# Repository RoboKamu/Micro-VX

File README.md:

<h1 align="center"> Micro-VX: Mini Audio Visualizer </h1>

<div align="center">
<i> Small portable STM32L4 based audio wave and FFT visualizer from electret microphone. This project started as an experiment to design my first PCB and explore the STM32L4 low-power MCU family. </i>
</div>

---

> This repository includes an extra project on the same board. The accelerometer visualization. That project was for expirementing with the module for future use. The main purpose for the board is for it to be used with the microphone, however a PCB error ment it had to be modified after assembly.
>

> Demo for expirimental Accelerometer Visualization:  
>
> Demo for FFT and Auido Wave Visualization: [Youtube Video Link](https://www.youtube.com/watch?v=JHZs5dUxs48)

---

### 1. Project structure

#### 1.1 Hardware

All Kicad source files for Schematic and PCB files are in the hardware folder. Also including Gerber files and footprint placement (assembly) for direct manufacturing, in this case JLCPCB. 

There are 2 versions of the PCB, with one being modified after assembly.

* **Accelerometer visualization:** 
Original PCB according to the schematic. Utilizing the Accelerometer (3-axis LIS2DW12) and I2C pin headers for OLED display (SSD1306).

* **Audio analyzer:**
Modified after assembly (refer to hardware folder). The PCB used for the audio analysis with electret microphone (B4013AM423-093). Also utilizes the I2C pin headers for OLED display (SSD1306) and a mechanical switch to change program state. 

#### 1.2 Firmware

In the firmware folder you will see 2 projects: 

* **The STM32L4-LIS2DW12-Visual project in the STM32L4-Accelerometer-Visual folder:**
Visualizer for the cheap accelerometer I added to the PCB. The program just shows the X, Y and Z axis as well as temperature. Another detail is to measure VDDA, this is very useful for sampling with ADC on battery powered devices. Ensuring accurate scaling. 

* **STM32L4-FW :**
The main project is this audio wave and FFT visualizer. Depending on the mechanical switch state (read from EXTI callback) it can either be showing continous audio wave or the FFT representation of it. Includes TIMER2 peripheral for triggering ADC to sample microphone, DMA double buffering, and I2C protocol for OLED display. The MCU was programmed with a ST-LINK V2, developed in STM32cubeIDE with HAL, and used the ARM cmsis library for DSP applications. 

### 2. Hardware Architecture
The PCB includes ESD protection and reverse polarity protection. Safe to use even if both battery and USB is connected because of the schottcky diode "OR", and the onboard LDO ensures a stable voltage for the STM32.  

Refer to the hardware folder for more specific information about the post assembly modification. 

The STM32L4 was chosen because it is from the low power series and also includes FPU and DSP. Not much flash memory is needed here so the 32 KB flash size was chosen. 

### 3. Firmware Architecture

#### 3.1 STM32L4-FW 

The firmware is rather simple. Timer2 TRGO initiate a conversion with a sample rate of 50 kHz. The ADC uses 8x oversampling with 1 bit shift to compensate low gain on hardware. DMA double buffer is used so wave visualizer does not have to wait for the whole fft buffer fill up and instead waits for the halv-transfer-complete flag. The FFT uses the ARM CMSIS library and all visual functionality in this project is scaled to the OLED.

Improvements could be made in terms of optimization and scaling, but that is outside the scope of this project.  

#### 3.2 STM32L4-LIS2DW12-Visual project 
Timer 2 triggers ADC injected group conversion, the callback function then stores the raw ADC value to a variable and sets a data ready flag

Timer 15 triggers normal ADC conversion, the callback function then stores the raw ADC value to a variable and sets a data ready flag

VDDA conversion just uses the last non zero value to calculate the voltage based on the formula from the datasheet. 

For the accelerometer the Data-Ready interrupt pin is connected to EXTI pin on microcontroller, when state changes on the pin the microcontroller notes this with a flag to later use in the superloop. 

### 4. Future improvements
This project was more of a practise so no real futher improvements are scheduled. One critical mistake that was overlooked was the usage of the microphone. The schematic PDF in the hardware folder shows no usage of preamp stage, this led to a bad resolution being sampled. For the PCB routing there are also obvious improvements to be made, but that will not be noted here. Below is an example of a improved schematic. The microphone preamp stage was validated via LTSpice simulation.

[revised-sch.pdf](https://github.com/user-attachments/files/25467140/revised-sch.pdf)

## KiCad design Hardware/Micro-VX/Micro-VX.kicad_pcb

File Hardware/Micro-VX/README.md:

Some revision has been made to the PCB. 

The PCB is based on the original schematic for microphone. This works correctly with the Accelerometer project, however, not with the audio analyzer. For the latter, a resistor has to be desoldered and another added. This is mentioned in the microphone section in the schematic. 

Below is an image showing the crude modification to the left, and the original PCBA to the right.

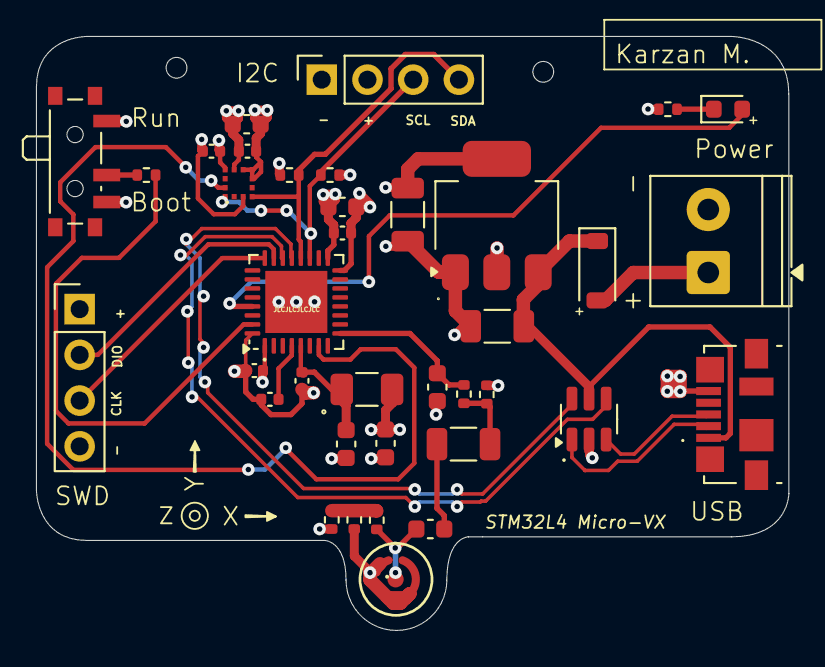
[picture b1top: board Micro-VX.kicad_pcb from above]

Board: 4 copper layers, 41.8 x 33.0 mm, 37 parts (0 on the bottom side), 24 nets.

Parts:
C1, C2, C7, C13, C14: 100n; C_0402_1005Metric
C3, C12, C15: 10u; C_0603_1608Metric
C4: 10n; C_0402_1005Metric
C5, C6: 1u; C_0603_1608Metric
C8, C9, C11: 22u; C_1206_3216Metric
C10: 22n; C_0603_1608Metric
D1: LED; LED_0603_1608Metric
D2: D_Schottky; D_SOD-123
FB1: 120R; Fuse_1206_3216Metric
J1: USB_B_Micro; USB_Micro-B_Molex_47346-0001
J2: Conn_01x04_Pin; PinHeader_1x04_P2.54mm_Vertical
J3: Conn_01x04_Socket; PinSocket_1x04_P2.54mm_Vertical
J4: Screw_Terminal_01x02; TerminalBlock_Phoenix_PT-1,5-2-3.5-H_1x02_P3.50mm_Horizontal
MIC1: B4013AM423-093; MIC-SMD_BD4.0_B4013AM423-093-1
R1, R5, R6: 10k; R_0402_1005Metric
R2: 1k5; R_0402_1005Metric
R3: 100; R_0402_1005Metric
R4: 330; R_0402_1005Metric
R7: 2k2; R_0402_1005Metric
R8: 1200; R_0402_1005Metric
R9: 2000; R_0402_1005Metric
SW1: SW_SPDT; SW_SPDT_PCM12
U1: STM32L432KBU6; QFN-32-1EP_5x5mm_P0.5mm_EP3.45x3.45mm
U2: AMS1117-3.3; SOT-223-3_TabPin2
U3: LIS2DW12_LGA-12
U4: USBLC6-2SC6; SOT-23-6

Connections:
+3.3V: C1.1, C2.1, C3.1, C6.1, C9.1, C12.1, C13.1, C14.1, FB1.2, J2.1, J3.2, R5.1, R6.1, R8.1, SW1.3 (C), U1.1 (VDD), U1.17 (VDD), U2.2 (VO), U3.9 (VDD), U3.10 (VDDIO)
+3.3VA: C4.1, C5.1, FB1.1, U1.5 (VDDA)
/USR_LED_K: D1.1 (K), R2.1
ACC_Pin: U1.7 (PA1), U3.12 (INT1)
ADC_In: C10.1, R3.2, U1.9 (PA3)
BOOT0: R1.2, U1.31 (PH3)
GND: C1.2, C2.2, C3.2, C4.2, C5.2, C6.2, C7.2, C8.2, C9.2, C10.2, C12.2, C13.2, C14.2, J1.5 (GND), J2.4, J3.1, J4.2, MIC1.2 (-), R2.2, R4.1, R9.1, SW1.1 (A), U1.16 (VSS), U1.32 (VSS), U1.33 (VSS), U2.1 (GND), U3.3 (SDO/SA0), U3.6 (GND), U3.7 (RES), U3.8 (GND), U4.2 (GND)
I2C1_SCL: J3.3, R5.2, U1.19 (PA9), U3.1 (SCL/SPC)
I2C1_SDA: J3.4, R6.2, U1.20 (PA10), U3.4 (SDA)
LED: D1.2 (A), U1.29 (PB6)
NRST: C7.1, U1.4 (NRST)
unnamed: C11.1, C15.2
unnamed: C11.2, R3.1, R4.2
unnamed: C15.1, MIC1.1 (+), R7.1
unnamed: R1.1, SW1.2 (B)
SWCLK: J2.3, U1.24 (PA14)
SWDIO: J2.2, U1.23 (PA13)
USB_CONN_D+: J1.3 (D+), U4.3 (I/O2)
USB_CONN_D-: J1.2 (D-), U4.1 (I/O1)
USB_D+: U1.22 (PA12), U4.4 (I/O2)
USB_D-: U1.21 (PA11), U4.6 (I/O1)
VBUS: C8.1, D2.1 (K), J1.1 (VBUS), U2.3 (VI), U4.5 (VBUS)
VDC: D2.2 (A), J4.1
V_mic: R7.2, R8.2, R9.2

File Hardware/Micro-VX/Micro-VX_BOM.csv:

"Reference","Qty","Value","Footprint","LCSC Part #"
"C1,C2,C7,C13,C14","5","100n","Capacitor_SMD:C_0402_1005Metric","C1525"
"C3,C12,C15","3","10u","Capacitor_SMD:C_0603_1608Metric","C19702"
"C4","1","10n","Capacitor_SMD:C_0402_1005Metric","C15195"
"C5,C6","2","1u","Capacitor_SMD:C_0603_1608Metric","C15849"
"C8,C9,C11","3","22u","Capacitor_SMD:C_1206_3216Metric","C12891"
"C10","1","22n","Capacitor_SMD:C_0603_1608Metric","C21122"
"D1","1","LED","LED_SMD:LED_0603_1608Metric","C2286"
"D2","1","D_Schottky","Diode_SMD:D_SOD-123","C74179"
"FB1","1","120R","Fuse:Fuse_1206_3216Metric","C14709"
"J1","1","USB_B_Micro","Connector_USB:USB_Micro-B_Molex_47346-0001","C132560"
"J2","1","Conn_01x04_Pin","Connector_PinHeader_2.54mm:PinHeader_1x04_P2.54mm_Vertical",""
"J3","1","Conn_01x04_Socket","Connector_PinSocket_2.54mm:PinSocket_1x04_P2.54mm_Vertical",""
"J4","1","Screw_Terminal_01x02","TerminalBlock_Phoenix:TerminalBlock_Phoenix_PT-1,5-2-3.5-H_1x02_P3.50mm_Horizontal",""
"MIC1","1","B4013AM423-093","MIC_B4013AM423-093:MIC-SMD_BD4.0_B4013AM423-093-1","C233790"
"R1,R5,R6","3","10k","Resistor_SMD:R_0402_1005Metric","C25744"
"R2","1","1k5","Resistor_SMD:R_0402_1005Metric","C25867"
"R3","1","100","Resistor_SMD:R_0402_1005Metric","C25076"
"R4","1","47k","Resistor_SMD:R_0402_1005Metric","C25076"
"R7","1","2k2","Resistor_SMD:R_0402_1005Metric","C25879"
"R8","1","1k2","Resistor_SMD:R_0402_1005Metric","C25862"
"R9","1","2k","Resistor_SMD:R_0402_1005Metric","C4109"
"SW1","1","SW_SPDT","Button_Switch_SMD:SW_SPDT_PCM12","C97433"
"U1","1","STM32L432KBU6","Package_DFN_QFN:QFN-32-1EP_5x5mm_P0.5mm_EP3.45x3.45mm","C94784"
"U2","1","AMS1117-3.3","Package_TO_SOT_SMD:SOT-223-3_TabPin2","C6186"
"U3","1","~","LIS2DW12:LIS2DW12_LGA-12","C189624"
"U4","1","USBLC6-2SC6","Package_TO_SOT_SMD:SOT-23-6","C7519"

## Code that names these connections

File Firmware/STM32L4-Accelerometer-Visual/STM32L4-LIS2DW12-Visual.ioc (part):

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Mcu.Name=STM32L432K(B-C)Ux
Mcu.Package=UFQFPN32
Mcu.UserName=STM32L432KBUx
PA1.GPIOParameters=GPIO_Label
PA1.GPIO_Label=ACC_INT
PA1.Signal=GPXTI1
PA10.Mode=I2C
PA10.Signal=I2C1_SDA
PA13\ (JTMS-SWDIO).Mode=Serial_Wire
PA13\ (JTMS-SWDIO).Signal=SYS_JTMS-SWDIO
PA14\ (JTCK-SWCLK).Mode=Serial_Wire
PA14\ (JTCK-SWCLK).Signal=SYS_JTCK-SWCLK
PA3.GPIOParameters=GPIO_Label
PA3.GPIO_Label=MIC_IN
PA3.Signal=ADCx_IN8
PA9.Mode=I2C
PA9.Signal=I2C1_SCL
PB6.GPIOParameters=GPIO_Label
PB6.GPIO_Label=LED
PB6.Signal=GPIO_Output
PH3-BOOT0.GPIOParameters=GPIO_Label
PH3-BOOT0.GPIO_Label=BOOT_SWITCH
PH3-BOOT0.Signal=GPIO_Input
RCC.HSE_VALUE=8000000
RCC.SYSCLKFreq_VALUE=64000000
RCC.SYSCLKSource=RCC_SYSCLKSOURCE_PLLCLK
board=custom

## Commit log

2025-10-04 Intial commit
2025-10-06 continous sampling works
2025-10-09 add MVP solution for audio and FFT spanning whole band
2025-10-09 finetune scaling and change max freq to 16 kHz for better visual
2025-10-10 Change FFT scaling and use lines instead of bars
    Also change audio wave to scale with RMS and increase I2C to fast mode (400 kHz)
2025-10-11 update hardware date
2026-02-22 Add future improvements section to README
    Added a section on future improvements and issues with the microphone usage.
